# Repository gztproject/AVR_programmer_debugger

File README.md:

# AVR_programmer_debugger

This is a Flipper zero breakout board with level shifters for AVR ISP programmer, UPDI programmer and UART debugger.

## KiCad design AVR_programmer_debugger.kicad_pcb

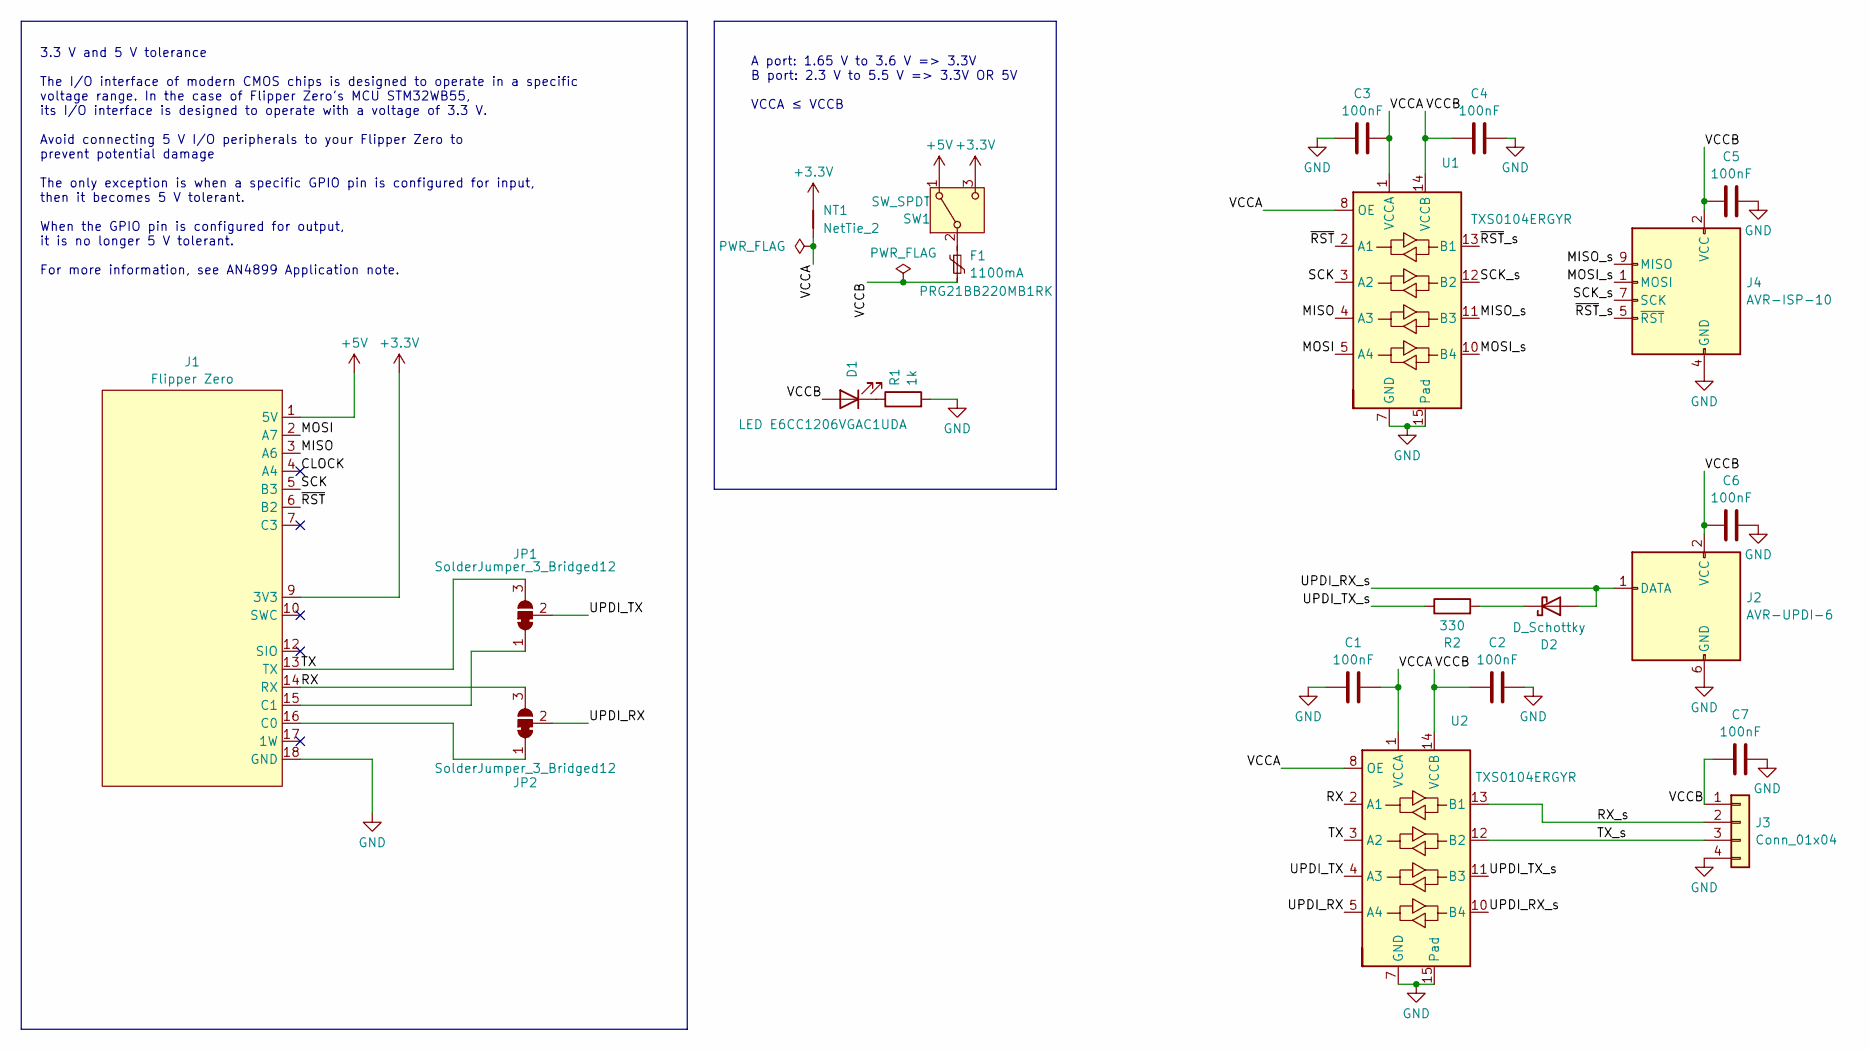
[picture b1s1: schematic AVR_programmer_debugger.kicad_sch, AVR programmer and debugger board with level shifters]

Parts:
C1, C2, C3, C4, C5, C6, C7: 100nF; C_0603_1608Metric
D1: LED E6CC1206VGAC1UDA; LED_1206_3216Metric_ReverseMount_Hole1.8x2.4mm
D2: D_Schottky; D_0603_1608Metric
F1: 1100mA; Fuse_0805_2012Metric; Part No PRG21BB220MB1RK
J1: Flipper Zero; Flipper zero
J2: AVR-UPDI-6; IDC-Header_2x03_P2.54mm_Vertical
J3: Conn_01x04; JST_XH_B4B-XH-A_1x04_P2.50mm_Vertical
J4: AVR-ISP-10; IDC-Header_2x05_P2.54mm_Vertical
JP1, JP2: SolderJumper_3_Bridged12; SolderJumper-3_P1.3mm_Bridged12_RoundedPad1.0x1.5mm
NT1: NetTie_2; NetTie-2_SMD_Pad0.5mm
R1: 1k; R_0603_1608Metric
R2: 330; R_0603_1608Metric
SW1: SW_SPDT; PinHeader_1x03_P2.54mm_Vertical
U1, U2: TXS0104ERGYR; Texas_S-PVQFN-N14_ThermalVias

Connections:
+3.3V: J1.9 (3V3), NT1.1, SW1.3 (C)
+5V: J1.1 (5V), SW1.1 (A)
/CLOCK: J1.4 (A4)
/MISO: J1.3 (A6), U1.4 (A3)
/MISO_s: J4.9 (MISO), U1.11 (B3)
/MOSI: J1.2 (A7), U1.5 (A4)
/MOSI_s: J4.1 (MOSI), U1.10 (B4)
/RX: J1.14 (RX), JP2.3 (B), U2.2 (A1)
/RX_s: J3.2, U2.13 (B1)
/SCK: J1.5 (B3), U1.3 (A2)
/SCK_s: J4.7 (SCK), U1.12 (B2)
/TX: J1.13 (TX), JP1.3 (B), U2.3 (A2)
/TX_s: J3.3, U2.12 (B2)
/UPDI_RX: JP2.2 (C), U2.5 (A4)
/UPDI_RX_s: D2.2 (A), J2.1 (DATA), U2.10 (B4)
/UPDI_TX: JP1.2 (C), U2.4 (A3)
/UPDI_TX_s: R2.1, U2.11 (B3)
/VCCA: C1.2, C3.2, NT1.2, U1.1 (VCCA), U1.8 (OE), U2.1 (VCCA), U2.8 (OE)
/VCCB: C2.1, C4.1, C5.1, C6.1, C7.1, D1.2 (A), F1.2, J2.2 (VCC), J3.1, J4.2 (VCC), U1.14 (VCCB), U2.14 (VCCB)
/~RST: J1.6 (B2), U1.2 (A1)
/~RST_s: J4.5 (~RST), U1.13 (B1)
GND: C1.1, C2.2, C3.1, C4.2, C5.2, C6.2, C7.2, J1.8 (GND), J1.11 (GND), J1.18 (GND), J2.6 (GND), J3.4, J4.4 (GND), J4.6 (GND), J4.8 (GND), J4.10 (GND), R1.2, U1.7 (GND), U1.15 (Pad), U2.7 (GND), U2.15 (Pad)
unnamed: D1.1 (K), R1.1
unnamed: D2.1 (K), R2.2
unnamed: J1.16 (C0), JP2.1 (A)
unnamed: J1.15 (C1), JP1.1 (A)
unnamed: F1.1, SW1.2 (B)

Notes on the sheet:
A port: 1.65 V to 3.6 V => 3.3V B port: 2.3 V to 5.5 V => 3.3V OR 5V VCCA ≤ VCCB
3.3 V and 5 V tolerance The I/O interface of modern CMOS chips is designed to operate in a specific voltage range. In the case of Flipper Zero's MCU STM32WB55, its I/O interface is designed to operate with a voltage of 3.3 V. Avoid connecting 5 V I/O peripherals to your Flipper Zero to prevent pote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

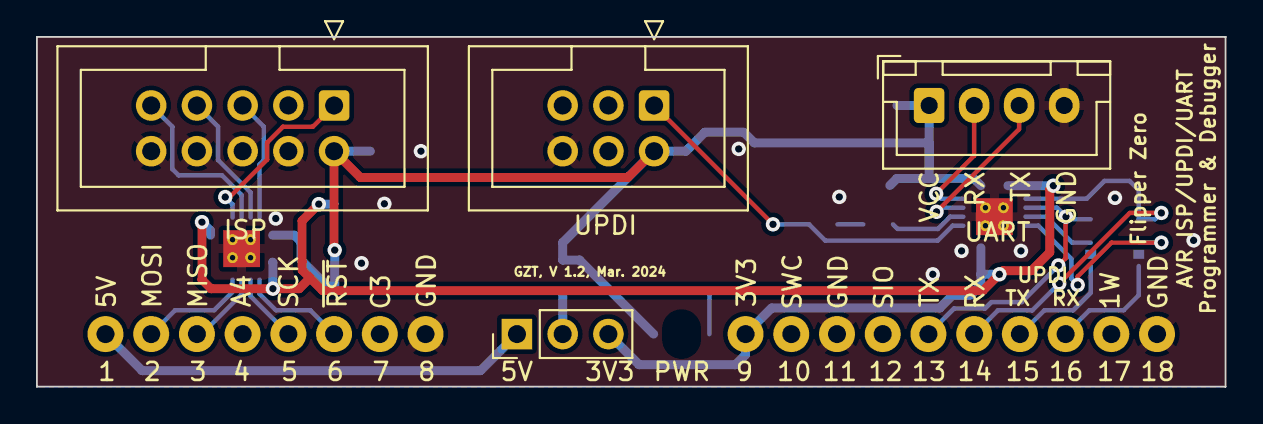
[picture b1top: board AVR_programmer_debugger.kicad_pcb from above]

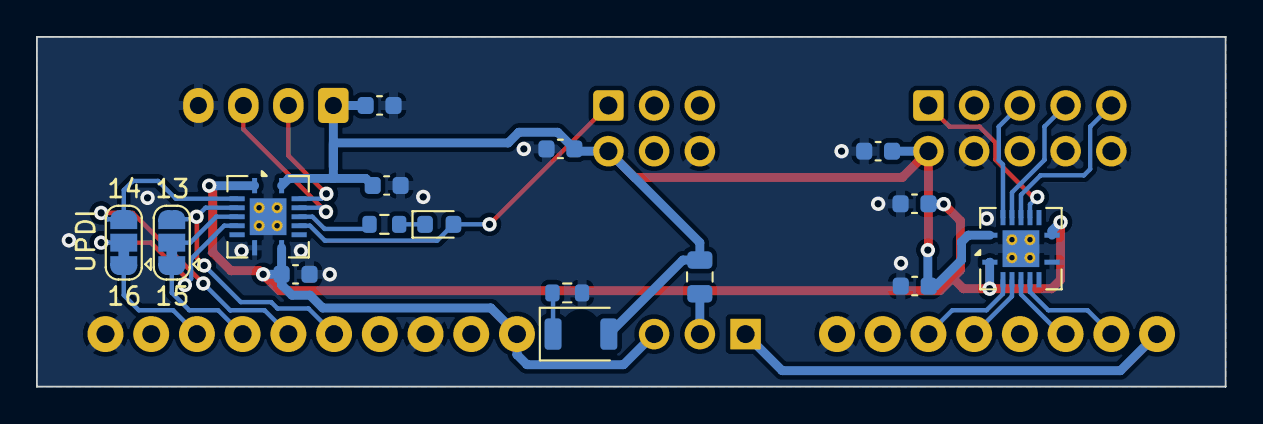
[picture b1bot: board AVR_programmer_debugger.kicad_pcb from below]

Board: 2 copper layers, 66.0 x 19.4 mm, 22 parts (17 on the bottom side), 26 nets.

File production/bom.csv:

Designator,Footprint,Quantity,Value,LCSC Part #
"C1, C2, C3, C4, C5, C6, C7",0603,7,100nF,
D1,1206,1,LED  E6CC1206VGAC1UDA,
D2,0603,1,D_Schottky,
F1,0805,1,1100mA,
J1,Flipper zero,1,Flipper Zero,
J2,IDC-Header_2x03_P2.54mm_Vertical,1,AVR-UPDI-6,
J3,JST_XH_B4B-XH-A_1x04_P2.50mm_Vertical,1,Conn_01x04,
J4,IDC-Header_2x05_P2.54mm_Vertical,1,AVR-ISP-10,
R1,0603,1,1k,
R2,0603,1,330,
SW1,PinHeader_1x03_P2.54mm_Vertical,1,SW_SPDT,
"U1, U2",Texas_S-PVQFN-N14_ThermalVias,2,TXS0104ERGYR,

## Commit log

2023-10-13 Rev1.0
2023-10-13 Edited gitignore
2023-10-13 Gitignore update
2023-10-13 Removed ignored files
2023-10-13 Added an image
2024-03-23 V1.2
